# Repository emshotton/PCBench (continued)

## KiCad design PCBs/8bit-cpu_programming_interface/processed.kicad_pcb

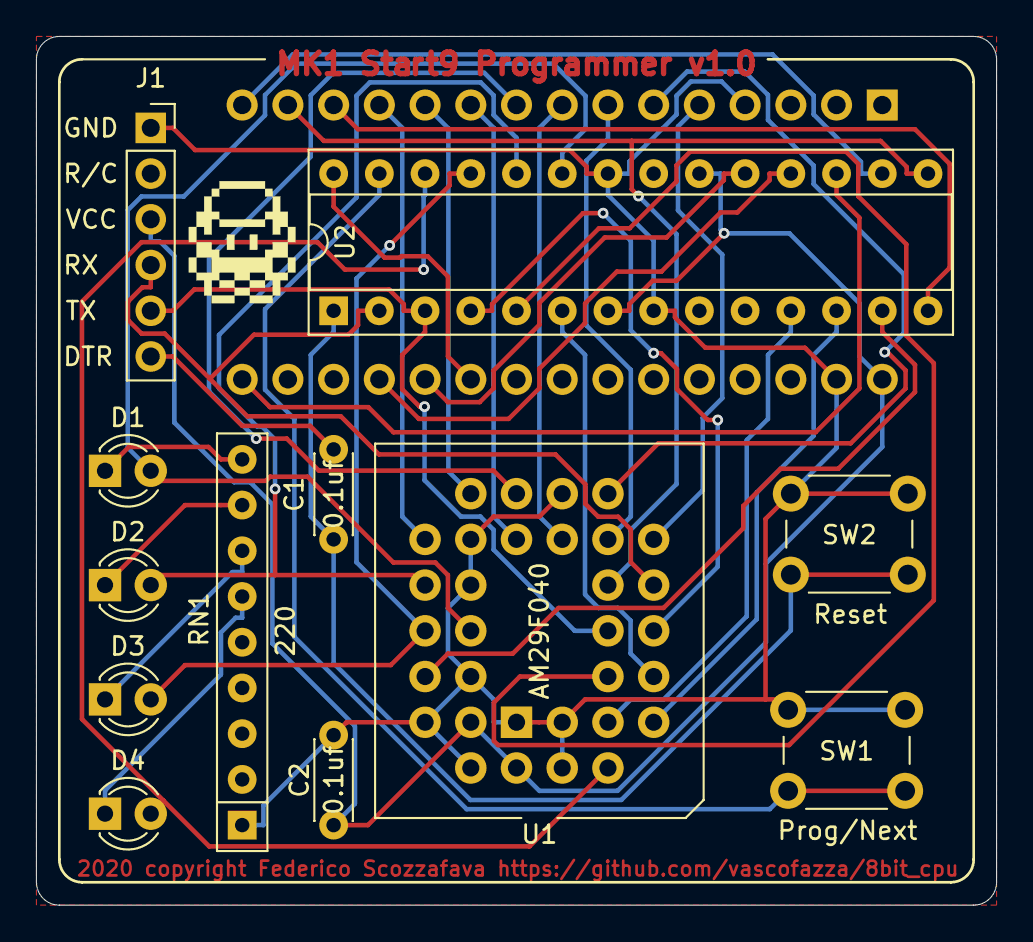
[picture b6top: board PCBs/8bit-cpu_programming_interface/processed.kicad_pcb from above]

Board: 2 copper layers, 53.3 x 48.3 mm, 15 parts (1 on the bottom side), 36 nets.

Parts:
A1: Arduino_Nano_Socket
C1, C2: 0.1uf; C_Disc_D4.3mm_W1.9mm_P5.00mm
D1, D2, D3, D4: LED_ALT; LED_D3.0mm
J1: Conn_01x06; PinSocket_1x06_P2.54mm_Vertical
RN1: 220; R_Array_SIP9
S0: LOGO; trainer_tiny
S1: LOGO; parrot_small
SW1: Prog/Next; SW_PUSH_6mm_H5mm
SW2: Reset; SW_PUSH_6mm_H5mm
U1: AM29F040; PLCC-32_THT-Socket
U2: ATmega328P-PU; DIP-28_W7.62mm_Socket

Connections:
GND: A1.GND1, A1.GND2, C2.2, J1.1, RN1.1, SW1.1, SW2.1, U1.1, U1.2, U1.3, U1.16, U1.22, U1.24, U1.28, U1.29, U1.30, U2.8, U2.22
unnamed: A1.A0, U2.18
unnamed: A1.A1, U2.19
unnamed: A1.A2, U2.28
unnamed: A1.D2, U1.13
unnamed: A1.D3, U1.14
unnamed: A1.D4, U1.15
unnamed: A1.D5, U1.17
unnamed: A1.D6, U1.18
unnamed: A1.D7, U1.19
unnamed: A1.D8, U1.20
unnamed: A1.D9, U1.21
unnamed: A1.D10, U2.14
unnamed: A1.D11, U1.12, U2.15
unnamed: A1.D12, U2.16
unnamed: A1.D13, U2.17
unnamed: C1.1, SW2.2, U2.1
unnamed: C1.2, J1.6
unnamed: D1.1, RN1.9
unnamed: D1.2, U1.26, U2.23
unnamed: D2.1, RN1.8
unnamed: D2.2, U1.23, U2.24
unnamed: D3.1, RN1.7
unnamed: D3.2, U1.25, U2.25
unnamed: D4.1, RN1.6
unnamed: D4.2, U1.4, U2.26
unnamed: J1.4, U1.11, U2.2
unnamed: J1.5, U1.10, U2.3
unnamed: SW1.2, U2.27
unnamed: U1.5, U2.12
unnamed: U1.6, U2.11
unnamed: U1.7, U2.6
unnamed: U1.8, U2.5
unnamed: U1.9, U2.4
unnamed: U1.27, U2.13
VCC: A1.VIN, C2.1, J1.3, U1.31, U1.32, U2.7, U2.20

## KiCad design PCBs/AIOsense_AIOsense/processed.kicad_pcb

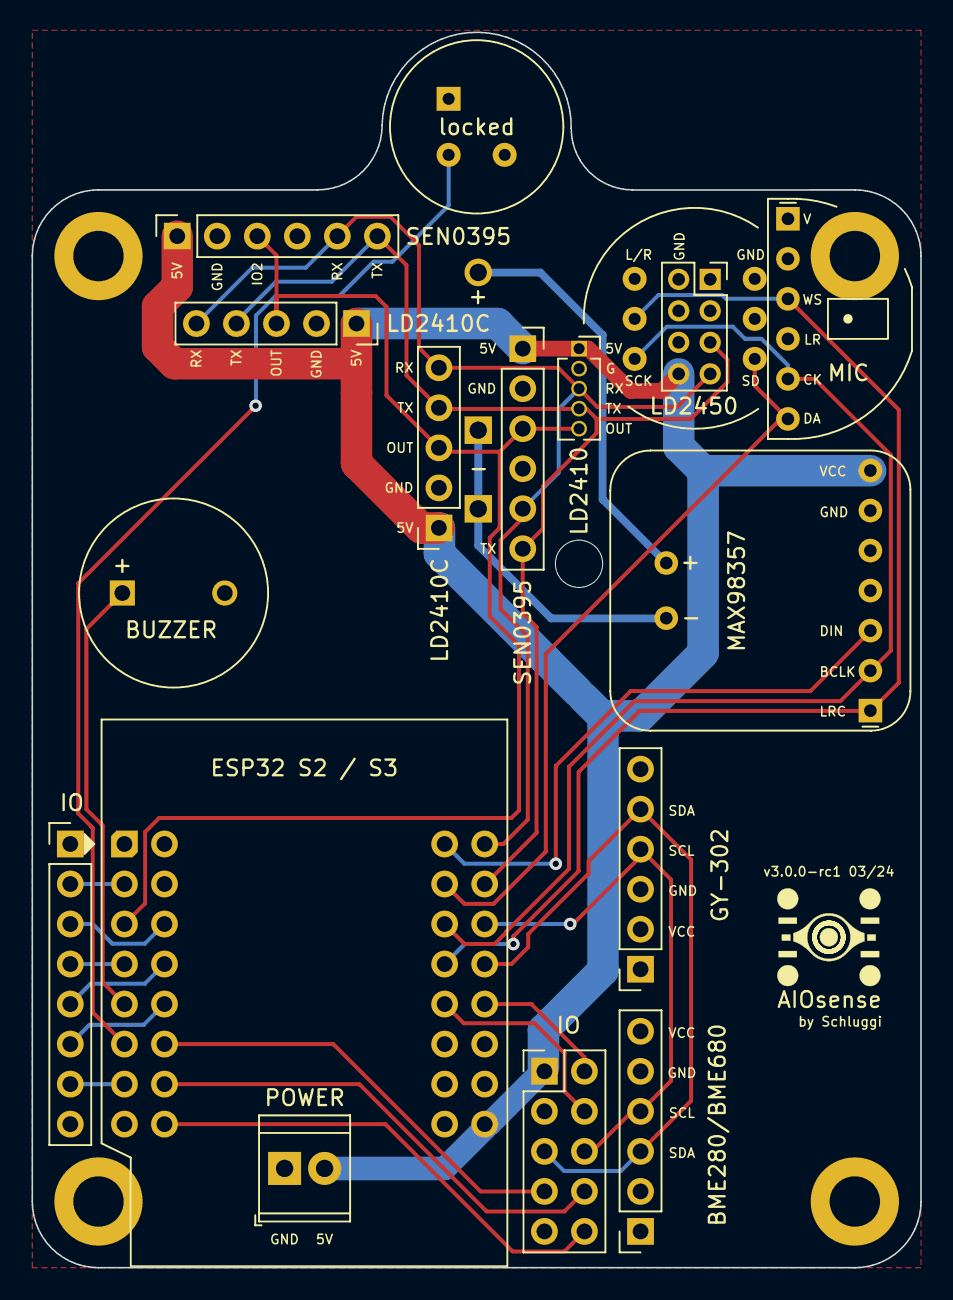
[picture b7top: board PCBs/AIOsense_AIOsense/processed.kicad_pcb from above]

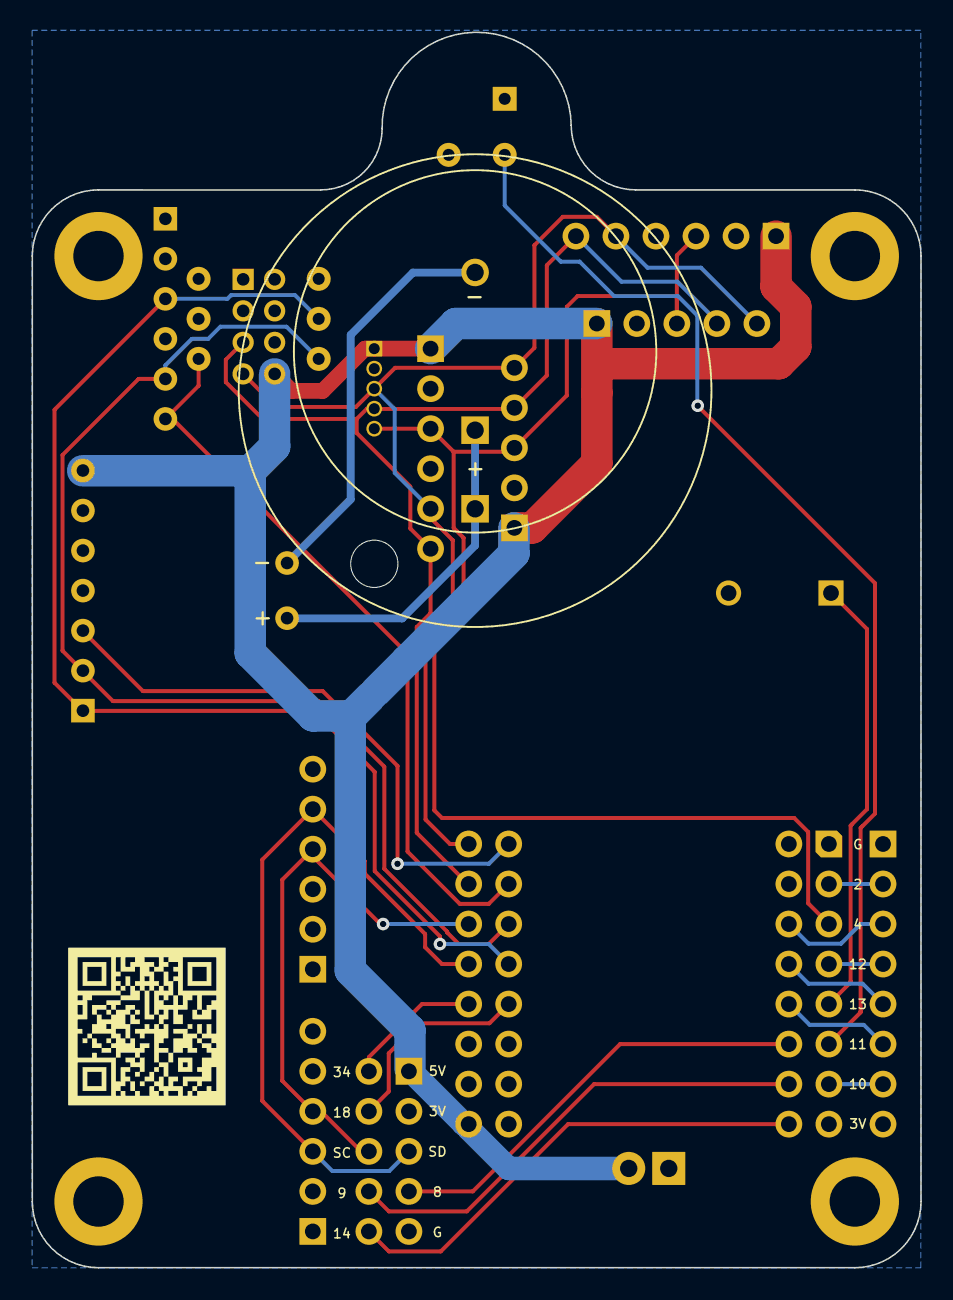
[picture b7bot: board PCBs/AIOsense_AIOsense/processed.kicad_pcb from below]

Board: 2 copper layers, 56.4 x 78.4 mm, 24 parts (2 on the bottom side), 27 nets.

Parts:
BZ1: RTTTL Buzzer; Buzzer_D12mm_P6.5mm
H1, H2, H3, H4: MountingHole; MountingHole_3.2mm_M3_DIN965_Pad
H5: SpeakerWireHole; Hole_Unplated_3.0mm
J1: external IO; PinHeader_2x05_P2.54mm_Vertical
J2: GY-302; PinSocket_1x06_P2.54mm_Vertical
J3: SEN0395; PinSocket_1x06_P2.54mm_Vertical
J4: SEN0395:alt; PinSocket_1x06_P2.54mm_Vertical
J5: external power; TerminalBlock_TE_282834-2_1x02_P2.54mm_Horizontal
J6: HLK-LD2410C; PinSocket_1x05_P2.54mm_Vertical
J7: BME280/BME680; PinSocket_1x06_P2.54mm_Vertical
J8: HLK-LD2410; PinSocket_1x05_P1.27mm_Vertical
J9: HLK-LD2410C:alt; PinSocket_1x05_P2.54mm_Vertical
J10: HLK-LD2450; PinSocket_2x04_P2.00mm_Vertical
J11: Conn_01x08_Pin; PinHeader_1x08_P2.54mm_Vertical
LS1: 2307; Speaker_2307
LS2: 3013; Speaker_3013
U1: EKMC1603111; PIR_EKMC1603111_TO-5
U2: WEMOS_S3_Mini
U3: MAX98357A; Adafruit_MAX98357A
U4: Sipeed_I2S_Mic
U5: INMP441

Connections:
+3V3: J1.3, J2.2, J7.6, J11.8, U1.1 (3V3), U2.8 (3V3), U4.1 (VDD), U5.2 (VDD)
+5V: J1.1, J3.1, J4.1, J5.2, J6.1, J8.1, J9.1, J10.8, U2.9 (5V), U3.7 (VIN)
BUZZER: BZ1.1 (-), U2.5 (GPIO13)
GND: BZ1.2 (+), J1.9, J2.3, J3.2, J4.2, J5.1, J6.2, J7.5, J8.2, J9.2, J10.2, J11.1, U1.3 (GND), U2.10 (GND), U2.26 (GND), U3.6 (GND), U4.2 (GND), U4.4 (L/R), U5.1 (GND), U5.4 (L/R)
GPIO2: J11.2, U2.2 (GPIO2)
GPIO5: J11.3, U2.19 (GPIO5)
GPIO6: J11.5, U2.20 (GPIO6)
GPIO7: J11.6, U2.21 (GPIO7)
GPIO8: J1.7, U2.22 (GPIO8)
GPIO9: J1.8, U2.23 (GPIO9)
GPIO10: J11.7, U2.7 (GPIO10)
GPIO12: J11.4, U2.4 (GPIO12)
GPIO14: J1.10, U2.24 (GPIO14)
GPIO18: J1.2, U2.12 (GPIO18)
GPIO21: J1.4, U2.28 (GPIO21)
I2S_CK: U2.30 (GPIO38), U3.2 (BCLK), U4.5 (CK), U5.6 (SCK)
I2S_IN: U2.31 (GPIO37), U4.6 (DA), U5.3 (SD)
I2S_OUT: U2.32 (GPIO33), U3.3 (DIN)
I2S_WS: U2.29 (GPIO34), U3.1 (LRCLK), U4.3 (WS), U5.5 (WS)
unnamed: LS2.2, U3.9 (SPK+)
unnamed: LS1.1, LS2.1, U3.8 (SPK-)
PIR: U1.2 (OUT), U2.6 (GPIO11)
SCL: J1.6, J2.4, J7.4, U2.14 (GPIO36)
SDA: J1.5, J2.5, J7.3, U2.13 (GPIO35)
U0RX: J3.5, J4.5, J6.5, J8.3, J9.5, J10.7, U2.16 (U0TXD)
U0TX: J3.6, J4.6, J6.4, J8.4, J9.4, J10.5, U2.15 (U0RXD)
mmWave: J3.3, J4.3, J6.3, J8.5, J9.3, U2.3 (GPIO4)
